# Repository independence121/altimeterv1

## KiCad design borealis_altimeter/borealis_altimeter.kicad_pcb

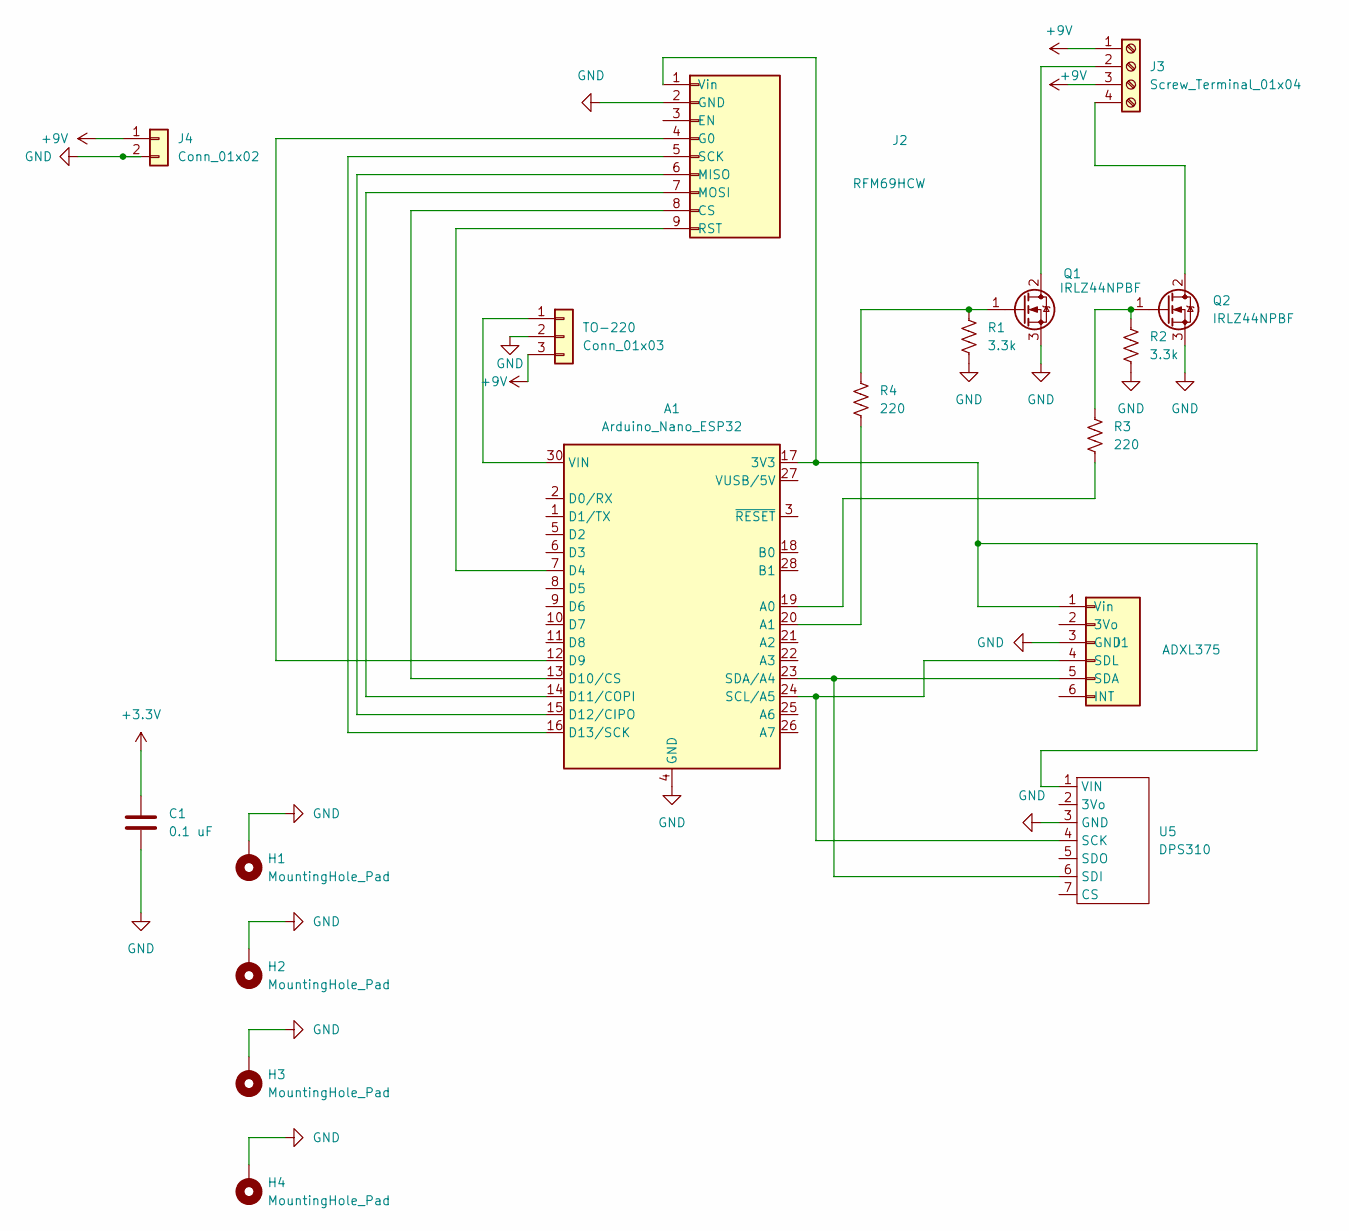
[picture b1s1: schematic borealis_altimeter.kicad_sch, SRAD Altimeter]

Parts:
A1: Arduino_Nano_ESP32; Arduino_Nano
C1: 0.1 uF; C_1206_3216Metric_Pad1.33x1.80mm_HandSolder
H1, H2, H3, H4: MountingHole_Pad; MountingHole_3.2mm_M3_Pad
J1: ADXL375; PinSocket_1x06_P2.54mm_Vertical
J2: RFM69HCW; PinSocket_1x09_P2.54mm_Vertical
J3: Screw_Terminal_01x04; TerminalBlock_Xinya_XY308-2.54-4P_1x04_P2.54mm_Horizontal
J4: Conn_01x02; JST_XH_B2B-XH-AM_1x02_P2.50mm_Vertical
Q1, Q2: IRLZ44NPBF; TO-220-3_Vertical
R1, R2: 3.3k; R_1210_3225Metric
R3, R4: 220; R_1210_3225Metric
TO-220: Conn_01x03; PinSocket_1x03_P2.54mm_Vertical
U5: DPS310; PinSocket_1x07_P2.54mm_Vertical

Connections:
+3.3V: C1.1
+9V: J3.1, J3.3, J4.1, TO-220.3
GND: A1.4 (GND), A1.29 (GND), C1.2, H1.1, H2.1, H3.1, H4.1, J1.3 (GND), J2.2 (GND), J4.2, Q1.3 (S), Q2.3 (S), R1.2, R2.2, TO-220.2, U5.3 (GND)
unnamed: A1.17 (3V3), J1.1 (Vin), J2.1 (Vin), U5.1 (VIN)
unnamed: A1.19 (A0), R3.1
unnamed: A1.20 (A1), R4.1
unnamed: A1.7 (D4), J2.9 (RST)
unnamed: A1.12 (D9), J2.4 (G0)
unnamed: A1.13 (D10/CS), J2.8 (CS)
unnamed: A1.14 (D11/COPI), J2.7 (MOSI)
unnamed: A1.15 (D12/CIPO), J2.6 (MISO)
unnamed: A1.16 (D13/SCK), J2.5 (SCK)
unnamed: A1.24 (SCL/A5), J1.4 (SDL), U5.4 (SCK)
unnamed: A1.23 (SDA/A4), J1.5 (SDA), U5.6 (SDI)
unnamed: A1.30 (VIN), TO-220.1
unnamed: J3.2, Q1.2 (D)
unnamed: J3.4, Q2.2 (D)
unnamed: Q1.1 (G), R1.1, R4.2
unnamed: Q2.1 (G), R2.1, R3.2

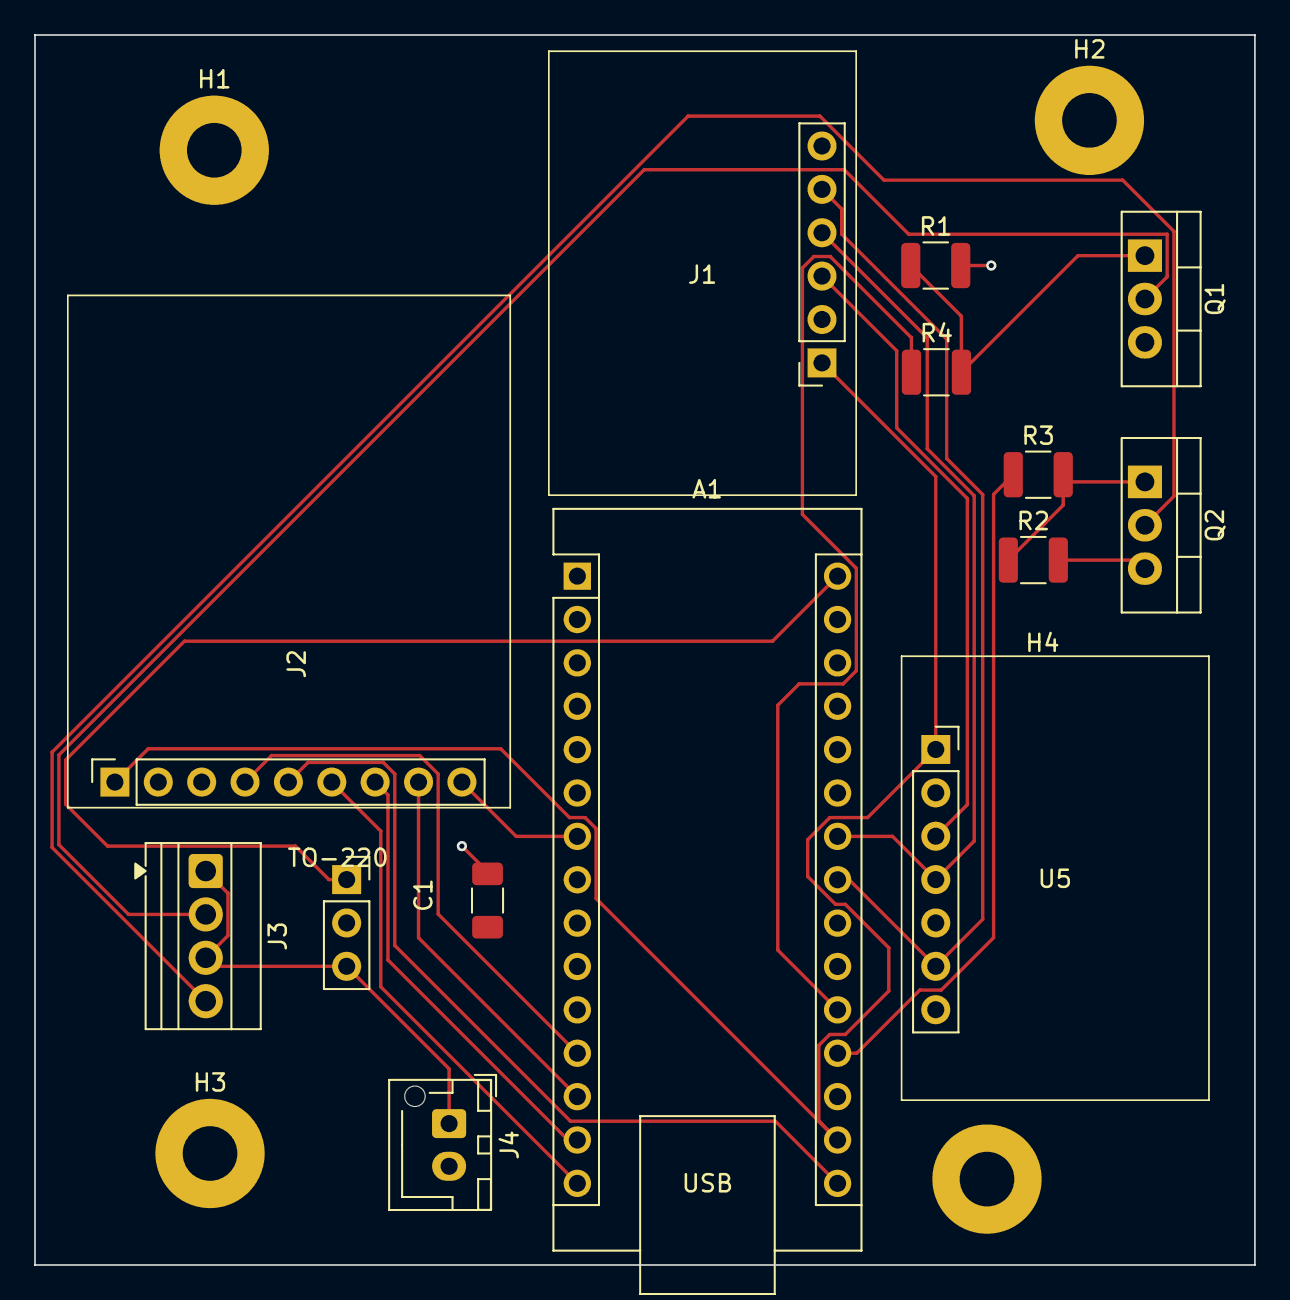
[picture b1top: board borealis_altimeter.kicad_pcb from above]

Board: 2 copper layers, 71.4 x 72.0 mm, 18 parts (0 on the bottom side), 18 nets.

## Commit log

2025-10-22 initial approach
2026-02-04 components
2026-02-04 oops
2026-03-02 removed gps
2026-03-04 added radio module
2026-03-04 changed out transistors
2026-03-04 updated footprints
2026-03-04 footprint updates
2026-03-04 the footprints have no errorsgit add .!
2026-03-06 resistors
2026-03-06 resistors on schematic lol
2026-03-10 jst connector and voltage regulator -- use 2s 7.4v battery
2026-03-10 module sizes
2026-03-11 boxes
2026-03-11 organized pcb layout
2026-03-11 added traces
2026-03-12 ground plane
2026-03-19 v1 of the pcb should be ready for printing???
2026-03-23 small corrections to pcb
2026-03-23 attempting to make gerber files
2026-03-23 gerber file attempts continue
2026-03-23 fixed traces yikes
2026-03-23 just cleaning up
2026-03-23 final gerber file
2026-04-06 nadia is great at measurements - again
2026-04-14 fixed i2c for adxl
2026-04-17 updated code
2026-04-20 updated radio schematic + renamed
2026-04-20 pcb v2
2026-04-20 small cleanup
2026-04-21 code cleanup
2026-04-28 schematic names
2026-05-01 unstaged changes
2026-05-21 new filtering logic for barometer
2026-05-21 bug fixes
2026-05-21 using classes now
2026-05-21 variable time for velocity calculation
2026-05-22 added support for old bmp280 based altimeter
2026-05-22 Delete deploymentlogic_v2 directory
    outdated code
2026-05-22 renamed for clarity (bmp388 code)
    git push
2026-05-22 changed naming scheme
